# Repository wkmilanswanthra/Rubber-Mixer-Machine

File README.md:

# Rubber Mixer v1.0

## :eyes: Special considerations when uploading code
* Always create a **_new branch_** to upload new and edited code
* Fetch origin before making any changes to your code
* Add a well written description to each commit
* Mention every single change done
* Create a pull request and merge the branch in the main after resolving any conflicts
* If you face any problems when merging a branch watch [this video](https://youtu.be/9j0AOrO0dnw?t=1086) or contact me :full_moon_with_face: 
* Use the seperate folder named "Proteus files" to upload any proteus project files 
* Use the seperate folder named "test2" to upload new or changed header files 

## Components that need to be completed
* - [ ] Code for the Ultrasonic sensor (Detect the liquid levels once before the LCD Display starts)
* - [ ] Code for the calculation of pH values and required volumes

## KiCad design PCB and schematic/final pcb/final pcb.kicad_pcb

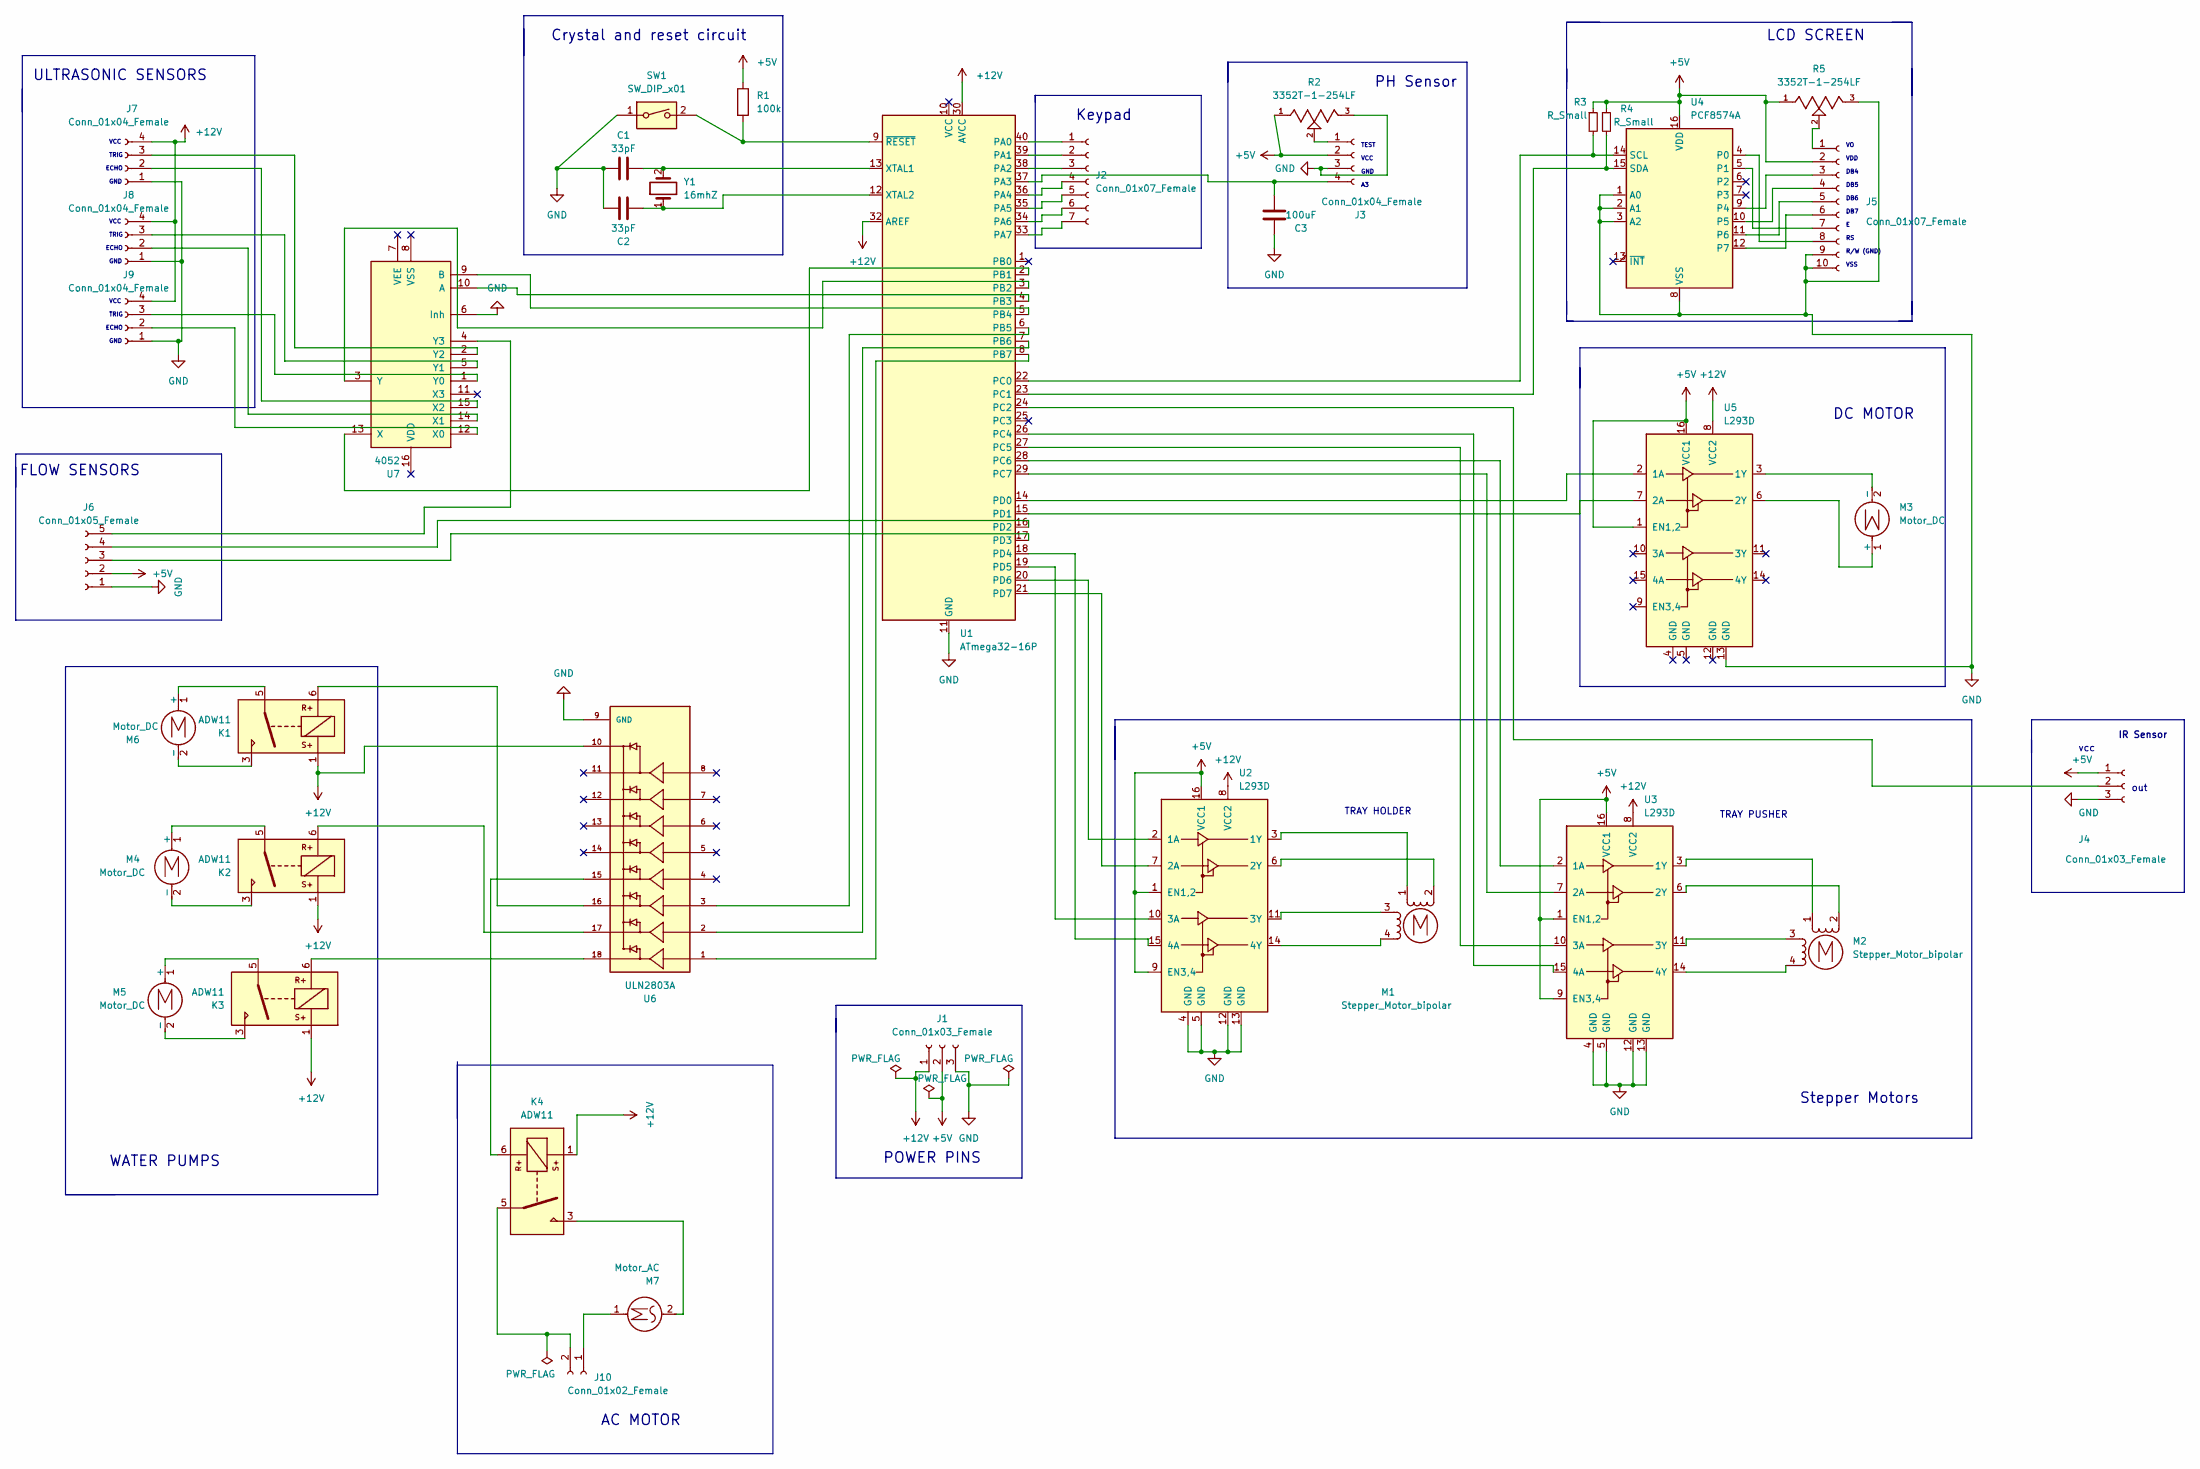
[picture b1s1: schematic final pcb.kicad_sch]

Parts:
C1: 33pF; C_Disc_D7.0mm_W2.5mm_P5.00mm
C2: 33pF; C_Disc_D7.5mm_W2.5mm_P5.00mm
C3: 100uF; C_Disc_D7.5mm_W2.5mm_P5.00mm
J1: Conn_01x03_Female; JST_EH_S3B-EH_1x03_P2.50mm_Horizontal
J2: Conn_01x07_Female; JST_EH_S7B-EH_1x07_P2.50mm_Horizontal
J3: Conn_01x04_Female; SolderWire-0.1sqmm_1x04_P3.6mm_D0.4mm_OD1mm
J4: Conn_01x03_Female; PinHeader_1x03_P2.54mm_Horizontal
J5: Conn_01x07_Female; JST_EH_S10B-EH_1x10_P2.50mm_Horizontal
J6: Conn_01x05_Female; JST_EH_S5B-EH_1x05_P2.50mm_Horizontal
J7, J8, J9: Conn_01x04_Female; JST_EH_S4B-EH_1x04_P2.50mm_Horizontal
J10: Conn_01x02_Female; JST_EH_B2B-EH-A_1x02_P2.50mm_Vertical
K1, K2, K3, K4: ADW11; Relay_1P1T_NO_10x24x18.8mm_Panasonic_ADW11xxxxW_THT
M1, M2: Stepper_Motor_bipolar; PinHeader_1x04_P2.54mm_Horizontal
M3, M4, M5, M6: Motor_DC; PinHeader_1x02_P2.54mm_Horizontal
M7: Motor_AC; PinHeader_1x02_P2.54mm_Horizontal
R1: 100k; R_Axial_DIN0204_L3.6mm_D1.6mm_P7.62mm_Horizontal
R2, R5: 3352T-1-254LF; TRIM_3352T-1-254LF; PARTREV 08/19
R3, R4: R_Small; R_0402_1005Metric
SW1: SW_DIP_x01; SW_DIP_SPSTx01_Slide_6.7x4.1mm_W7.62mm_P2.54mm_LowProfile
U1: ATmega32-16P; DIP-40_W15.24mm
U2, U3, U5: L293D; DIP-16_W7.62mm
U4: PCF8574A; SOIC127P1030X265-16N
U6: ULN2803A; DIP850W46P254L2324H393Q18; PARTREV 4
U7: 4052; DIP794W45P254L1969H508Q16
Y1: 16mhZ; Crystal_C38-LF_D3.0mm_L8.0mm_Vertical

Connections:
+5V: J1.2, J3.2, J4.1, J5.2, J6.2, R1.1, R2.1, R3.1, R4.1, R5.1, U2.1 (EN1,2), U2.9 (EN3,4), U2.16 (VCC1), U3.1 (EN1,2), U3.9 (EN3,4), U3.16 (VCC1), U4.16 (VDD), U5.1 (EN1,2), U5.16 (VCC1)
+12V: J1.1, J7.4, J8.4, J9.4, K1.1, K2.1, K3.1, K4.1, U1.30 (AVCC), U1.32 (AREF), U2.8 (VCC2), U3.8 (VCC2), U5.8 (VCC2), U6.10
GND: C1.2, C2.2, C3.2, J1.3, J3.3, J4.3, J5.9, J5.10, J6.1, J7.1, J8.1, J9.1, R2.3, R5.3, SW1.1, U1.11 (GND), U1.31 (GND), U2.4 (GND), U2.5 (GND), U2.12 (GND), U2.13 (GND), U3.4 (GND), U3.5 (GND), U3.12 (GND), U3.13 (GND), U4.1 (A0), U4.2 (A1), U4.3 (A2), U4.8 (VSS), U5.13 (GND), U6.9 (GND), U7.6 (Inh)
unnamed: C1.1, U1.13 (XTAL1), Y1.2
unnamed: C2.1, U1.12 (XTAL2), Y1.1
unnamed: C3.1, J3.4, U1.37 (PA3)
unnamed: J2.1, U1.40 (PA0)
unnamed: J2.2, U1.39 (PA1)
unnamed: J2.3, U1.38 (PA2)
unnamed: J2.4, U1.36 (PA4)
unnamed: J2.5, U1.35 (PA5)
unnamed: J2.6, U1.34 (PA6)
unnamed: J2.7, U1.33 (PA7)
unnamed: J3.1, R2.2
unnamed: J4.2, U1.24 (PC2)
unnamed: J5.1, R5.2
unnamed: J5.3, U4.9 (P4)
unnamed: J5.4, U4.10 (P5)
unnamed: J5.5, U4.11 (P6)
unnamed: J5.6, U4.12 (P7)
unnamed: J5.7, U4.5 (P1)
unnamed: J5.8, U4.4 (P0)
unnamed: J6.3, U1.17 (PD3)
unnamed: J6.4, U1.16 (PD2)
unnamed: J6.5, U7.4 (Y3)
unnamed: J7.2, U7.15 (X2)
unnamed: J7.3, U7.2 (Y2)
unnamed: J8.2, U7.14 (X1)
unnamed: J8.3, U7.5 (Y1)
unnamed: J9.2, U7.12 (X0)
unnamed: J9.3, U7.1 (Y0)
unnamed: J10.1, M7.1
unnamed: J10.2, K4.5
unnamed: K1.3, M6.2 (-)
unnamed: K1.5, M6.1 (+)
unnamed: K1.6, U6.16
unnamed: K2.3, M4.2 (-)
unnamed: K2.5, M4.1 (+)
unnamed: K2.6, U6.17
unnamed: K3.3, M5.2 (-)
unnamed: K3.5, M5.1 (+)
unnamed: K3.6, U6.18
unnamed: K4.3, M7.2
unnamed: K4.6, U6.15
unnamed: M1.1, U2.3 (1Y)
unnamed: M1.2 (-), U2.6 (2Y)
unnamed: M1.3, U2.11 (3Y)
unnamed: M1.4, U2.14 (4Y)
unnamed: M2.1, U3.3 (1Y)
unnamed: M2.2 (-), U3.6 (2Y)
unnamed: M2.3, U3.11 (3Y)
unnamed: M2.4, U3.14 (4Y)
unnamed: M3.1 (+), U5.6 (2Y)
unnamed: M3.2 (-), U5.3 (1Y)
unnamed: R1.2, SW1.2, U1.9 (~RESET)
unnamed: R3.2, U1.22 (PC0), U4.14 (SCL)
unnamed: R4.2, U1.23 (PC1), U4.15 (SDA)
unnamed: U1.2 (PB1), U7.13 (X)
unnamed: U1.3 (PB2), U7.3 (Y)
unnamed: U1.4 (PB3), U7.10 (A)
unnamed: U1.5 (PB4), U7.9 (B)
unnamed: U1.6 (PB5), U6.3
unnamed: U1.7 (PB6), U6.2
unnamed: U1.8 (PB7), U6.1
unnamed: U1.14 (PD0), U5.2 (1A)
unnamed: U1.15 (PD1), U5.7 (2A)
unnamed: U1.18 (PD4), U2.15 (4A)
unnamed: U1.19 (PD5), U2.10 (3A)
unnamed: U1.20 (PD6), U2.2 (1A)
unnamed: U1.21 (PD7), U2.7 (2A)
unnamed: U1.26 (PC4), U3.15 (4A)
unnamed: U1.27 (PC5), U3.10 (3A)
unnamed: U1.28 (PC6), U3.2 (1A)
unnamed: U1.29 (PC7), U3.7 (2A)

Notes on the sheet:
TRIG
GND
TRAY PUSHER
DC MOTOR
VCC
R/W (GND)
VSS
out
VDD
AC MOTOR
FLOW SENSORS
ECHO
DB5
DB7
PH Sensor
LCD SCREEN
DB4
Crystal and reset circuit
IR Sensor
vcc
ULTRASONIC SENSORS
TRAY HOLDER
WATER PUMPS
TEST
Keypad
POWER PINS
Stepper Motors
DB6

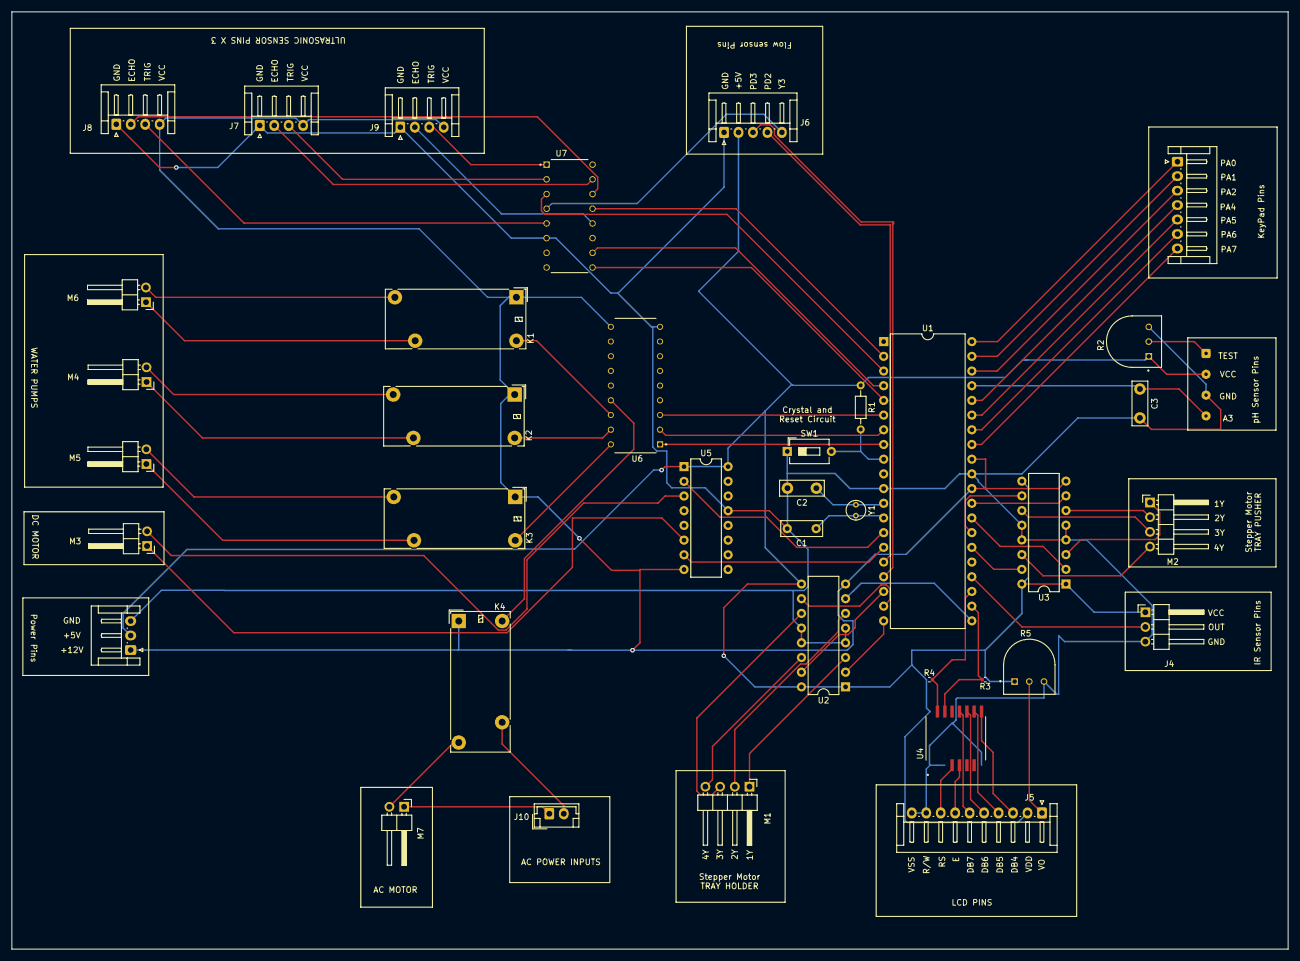
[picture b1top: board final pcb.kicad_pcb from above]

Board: 2 copper layers, 220.6 x 162.0 mm, 38 parts (0 on the bottom side), 74 nets.

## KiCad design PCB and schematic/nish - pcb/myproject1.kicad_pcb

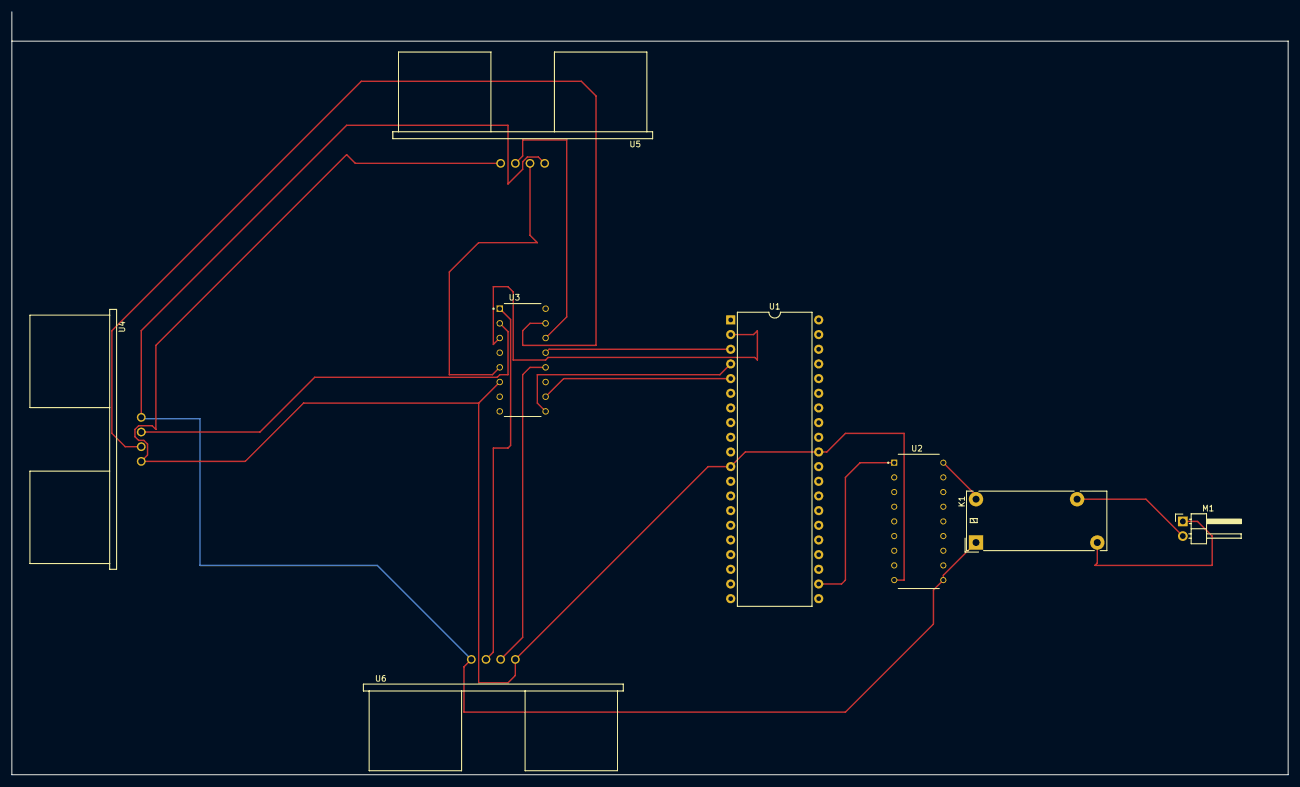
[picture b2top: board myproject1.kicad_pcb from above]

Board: 2 copper layers, 221.0 x 132.1 mm, 8 parts (0 on the bottom side), 16 nets.

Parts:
K1: ADW11; Relay_1P1T_NO_10x24x18.8mm_Panasonic_ADW11xxxxW_THT
M1: Motor_AC; PinHeader_1x02_P2.54mm_Horizontal
U1: ATmega32L-8P; DIP-40_W15.24mm
U2: ULN2803A; DIP850W46P254L2324H393Q18
U3: CD4052B; DIP794W45P254L1969H508Q16
U4, U5, U6: HC-SR04; XCVR_HC-SR04

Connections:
+12V: K1.1, U2.10 (COM), U4.1 (VCC), U5.1 (VCC), U6.1 (VCC)
AC: K1.5, M1.2
Earth: U1.11 (GND), U1.31 (GND), U2.9 (GND), U3.6 (INH), U4.4 (GND), U5.4 (GND), U6.4 (GND)
unnamed: K1.3, M1.1
unnamed: K1.6, U2.18 (O1)
unnamed: U1.2 (PB1), U3.3 (Y)
unnamed: U1.3 (PB2), U3.13 (X)
unnamed: U1.4 (PB3), U3.9 (B)
unnamed: U1.5 (PB4), U3.10 (A)
unnamed: U1.22 (PC0), U2.1 (I1)
unnamed: U3.1 (Y0), U6.2 (TRIG)
unnamed: U3.2 (Y2), U4.2 (TRIG)
unnamed: U3.5 (Y1), U5.2 (TRIG)
unnamed: U3.12 (X0), U6.3 (ECHO)
unnamed: U3.14 (X1), U5.3 (ECHO)
unnamed: U3.15 (X2), U4.3 (ECHO)

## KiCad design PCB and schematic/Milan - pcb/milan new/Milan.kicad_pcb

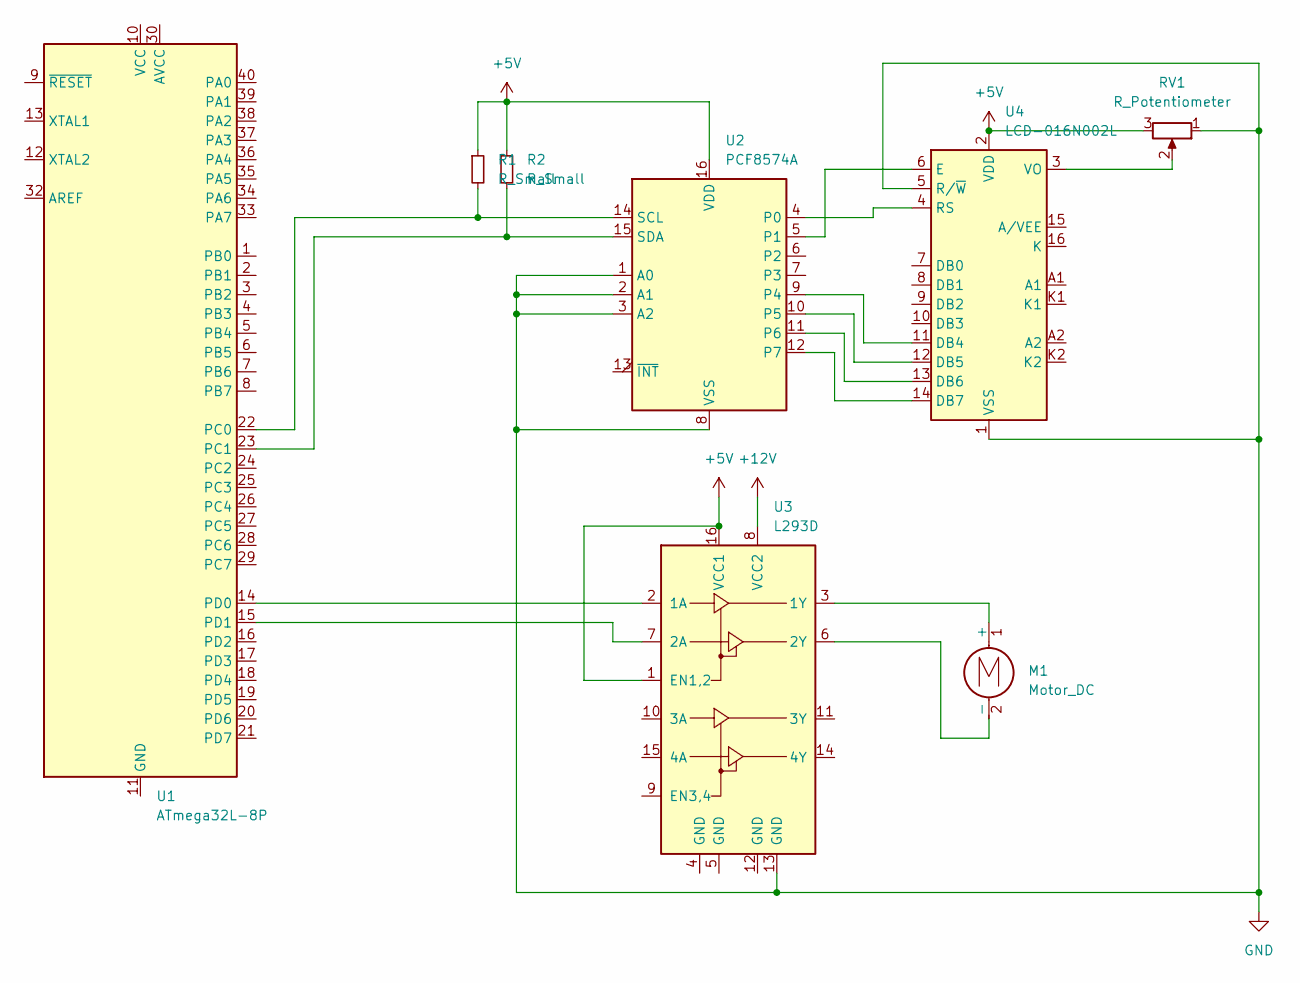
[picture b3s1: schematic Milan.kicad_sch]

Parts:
M1: Motor_DC; PinHeader_1x02_P2.54mm_Horizontal
R1, R2: R_Small; R_0402_1005Metric
RV1: R_Potentiometer; Potentiometer_ACP_CA6-VSMD_Vertical
U1: ATmega32L-8P; DIP-40_W15.24mm
U2: PCF8574A; DIL16
U3: L293D; DIP-16_W7.62mm
U4: LCD-016N002L

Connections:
+5V: R1.1, R2.1, RV1.3, U2.16 (VDD), U3.1 (EN1,2), U3.16 (VCC1), U4.2 (VDD)
+12V: U3.8 (VCC2)
GND: RV1.1, U2.1 (A0), U2.2 (A1), U2.3 (A2), U2.8 (VSS), U3.13 (GND), U4.1 (VSS), U4.5 (R/~W)
unnamed: M1.1 (+), U3.3 (1Y)
unnamed: M1.2 (-), U3.6 (2Y)
unnamed: U1.11 (GND), U1.31 (GND)
unnamed: U1.14 (PD0), U3.2 (1A)
unnamed: U1.15 (PD1), U3.7 (2A)
unnamed: R1.2, U1.22 (PC0), U2.14 (SCL)
unnamed: R2.2, U1.23 (PC1), U2.15 (SDA)
unnamed: U2.4 (P0), U4.4 (RS)
unnamed: U2.5 (P1), U4.6 (E)
unnamed: U2.9 (P4), U4.11 (DB4)
unnamed: U2.10 (P5), U4.12 (DB5)
unnamed: U2.11 (P6), U4.13 (DB6)
unnamed: U2.12 (P7), U4.14 (DB7)
unnamed: RV1.2, U4.3 (VO)

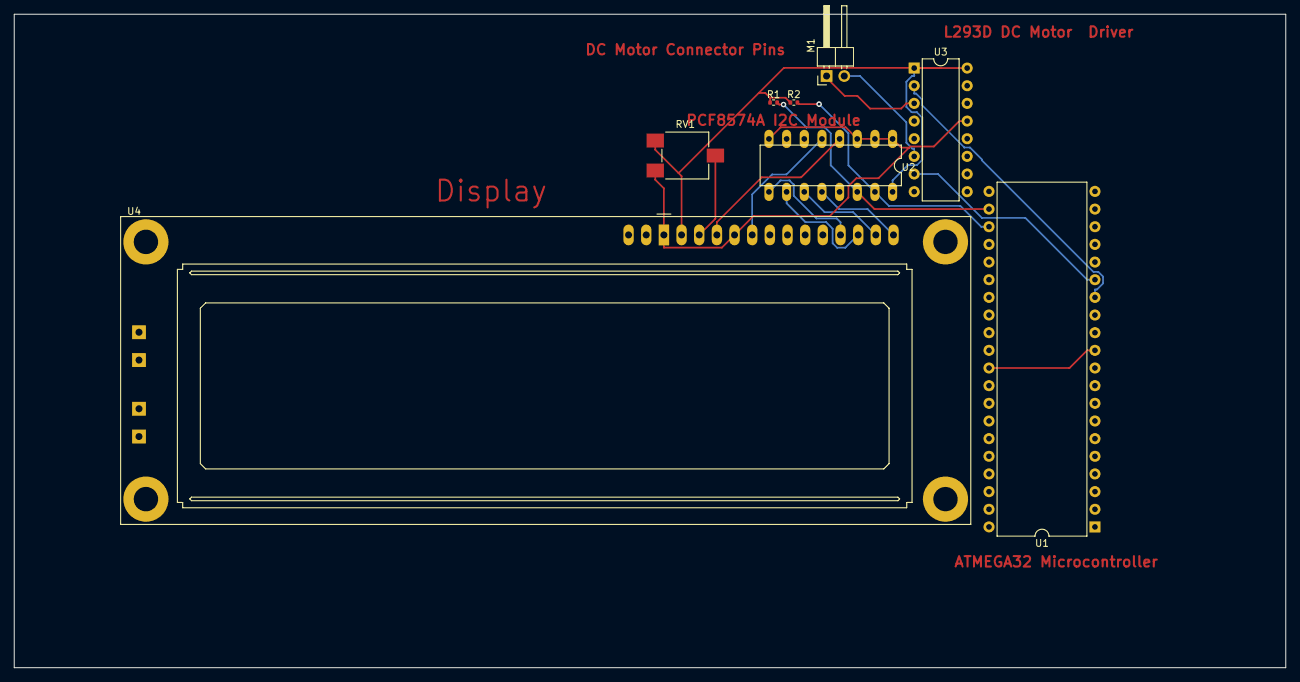
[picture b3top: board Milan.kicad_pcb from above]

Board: 2 copper layers, 182.9 x 94.0 mm, 8 parts (0 on the bottom side), 16 nets.

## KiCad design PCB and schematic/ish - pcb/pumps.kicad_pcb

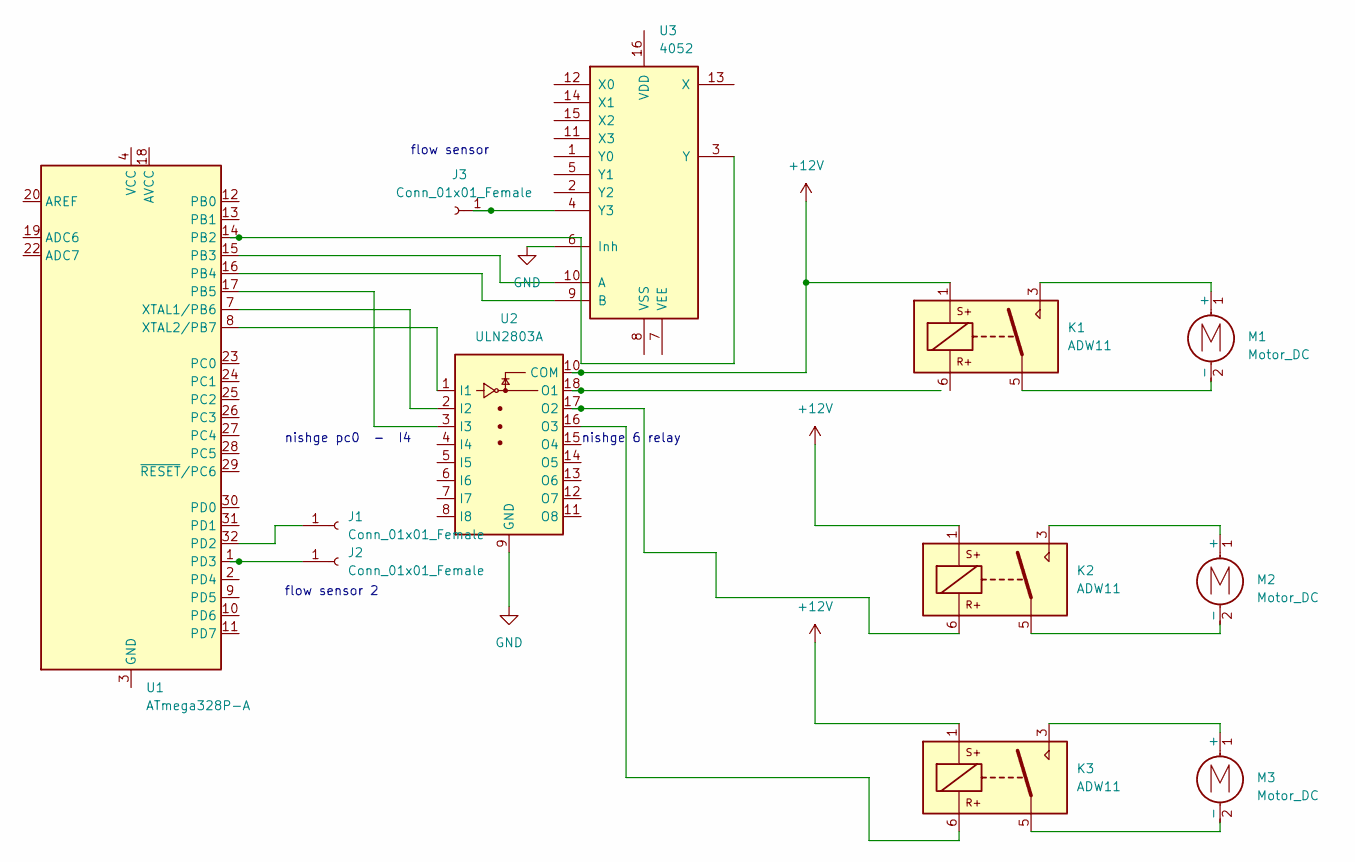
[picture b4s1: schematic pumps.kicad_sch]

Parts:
J1, J2, J3: Conn_01x01_Female; PinHeader_1x02_P1.00mm_Horizontal
K1, K2, K3: ADW11; Relay_1P1T_NO_10x24x18.8mm_Panasonic_ADW11xxxxW_THT
M1, M2, M3: Motor_DC; PinHeader_1x02_P2.54mm_Horizontal
U1: ATmega328P-A; TQFP-32_7x7mm_P0.8mm
U2: ULN2803A; DIP850W46P254L2324H393Q18
U3: 4052; DIP794W45P254L1969H508Q16

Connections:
+12V: K1.1, K2.1, K3.1, U2.10 (COM)
GND: U2.9 (GND), U3.6 (Inh)
unnamed: K1.3, M1.1 (+)
unnamed: K1.5, M1.2 (-)
unnamed: K2.3, M2.1 (+)
unnamed: K2.5, M2.2 (-)
unnamed: K2.6, U2.17 (O2)
unnamed: K3.3, M3.1 (+)
unnamed: K3.5, M3.2 (-)
unnamed: K3.6, U2.16 (O3)
unnamed: J2.1, U1.1 (PD3)
unnamed: U1.4 (VCC), U1.6 (VCC)
unnamed: U1.7 (XTAL1/PB6), U2.2 (I2)
unnamed: U1.8 (XTAL2/PB7), U2.1 (I1)
unnamed: U1.14 (PB2), U3.3 (Y)
unnamed: U1.15 (PB3), U3.10 (A)
unnamed: U1.16 (PB4), U3.9 (B)
unnamed: U1.17 (PB5), U2.3 (I3)
unnamed: U1.3 (GND), U1.5 (GND), U1.21 (GND)
unnamed: J1.1, U1.32 (PD2)
unnamed: J3.1, U3.4 (Y3)

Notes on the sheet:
nishge pc0 - I4
nishge 6 relay
flow sensor
flow sensor 2

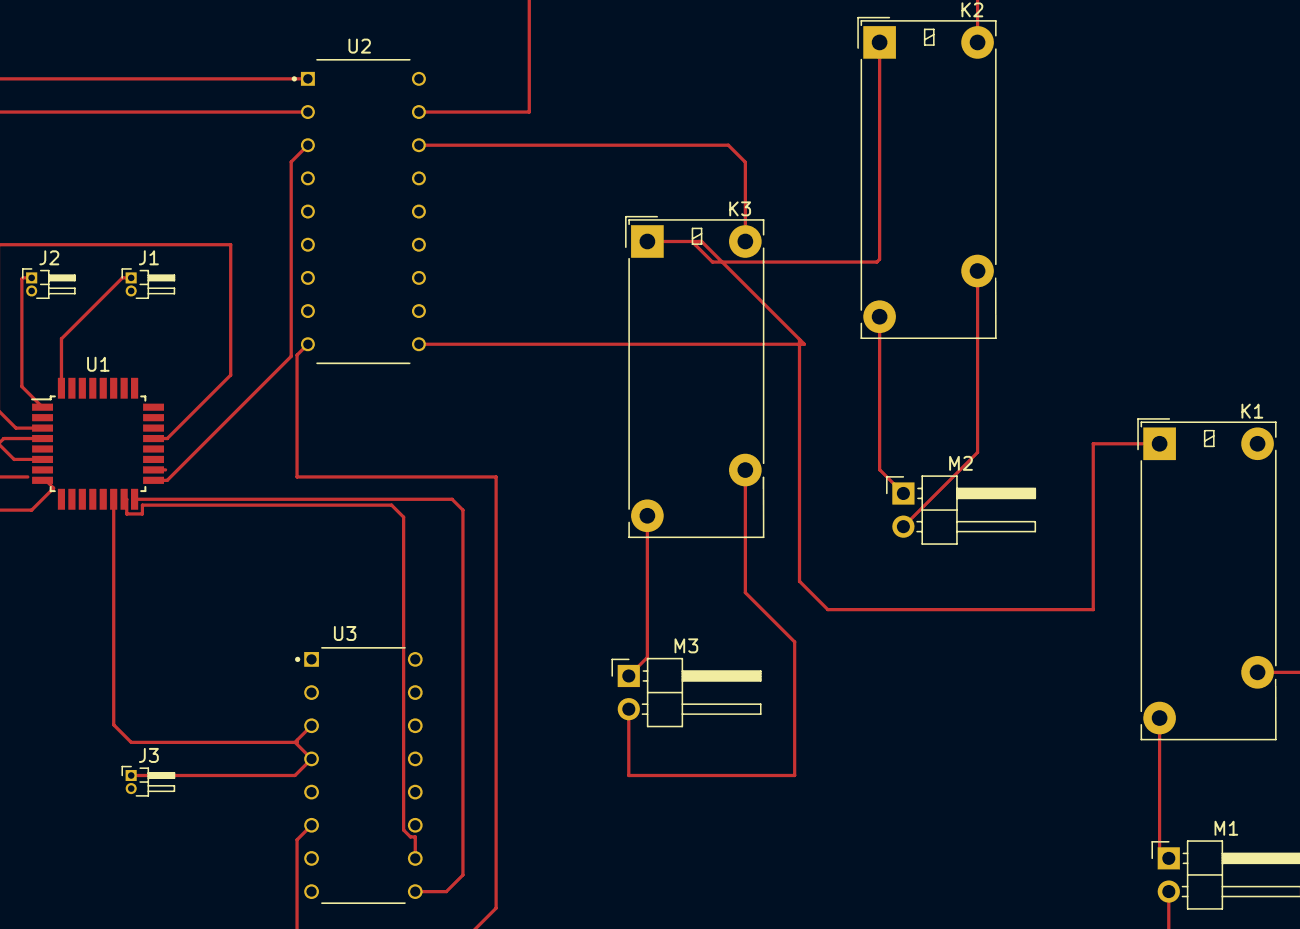
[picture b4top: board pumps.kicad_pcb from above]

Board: 2 copper layers, 12 parts (0 on the bottom side), 21 nets.

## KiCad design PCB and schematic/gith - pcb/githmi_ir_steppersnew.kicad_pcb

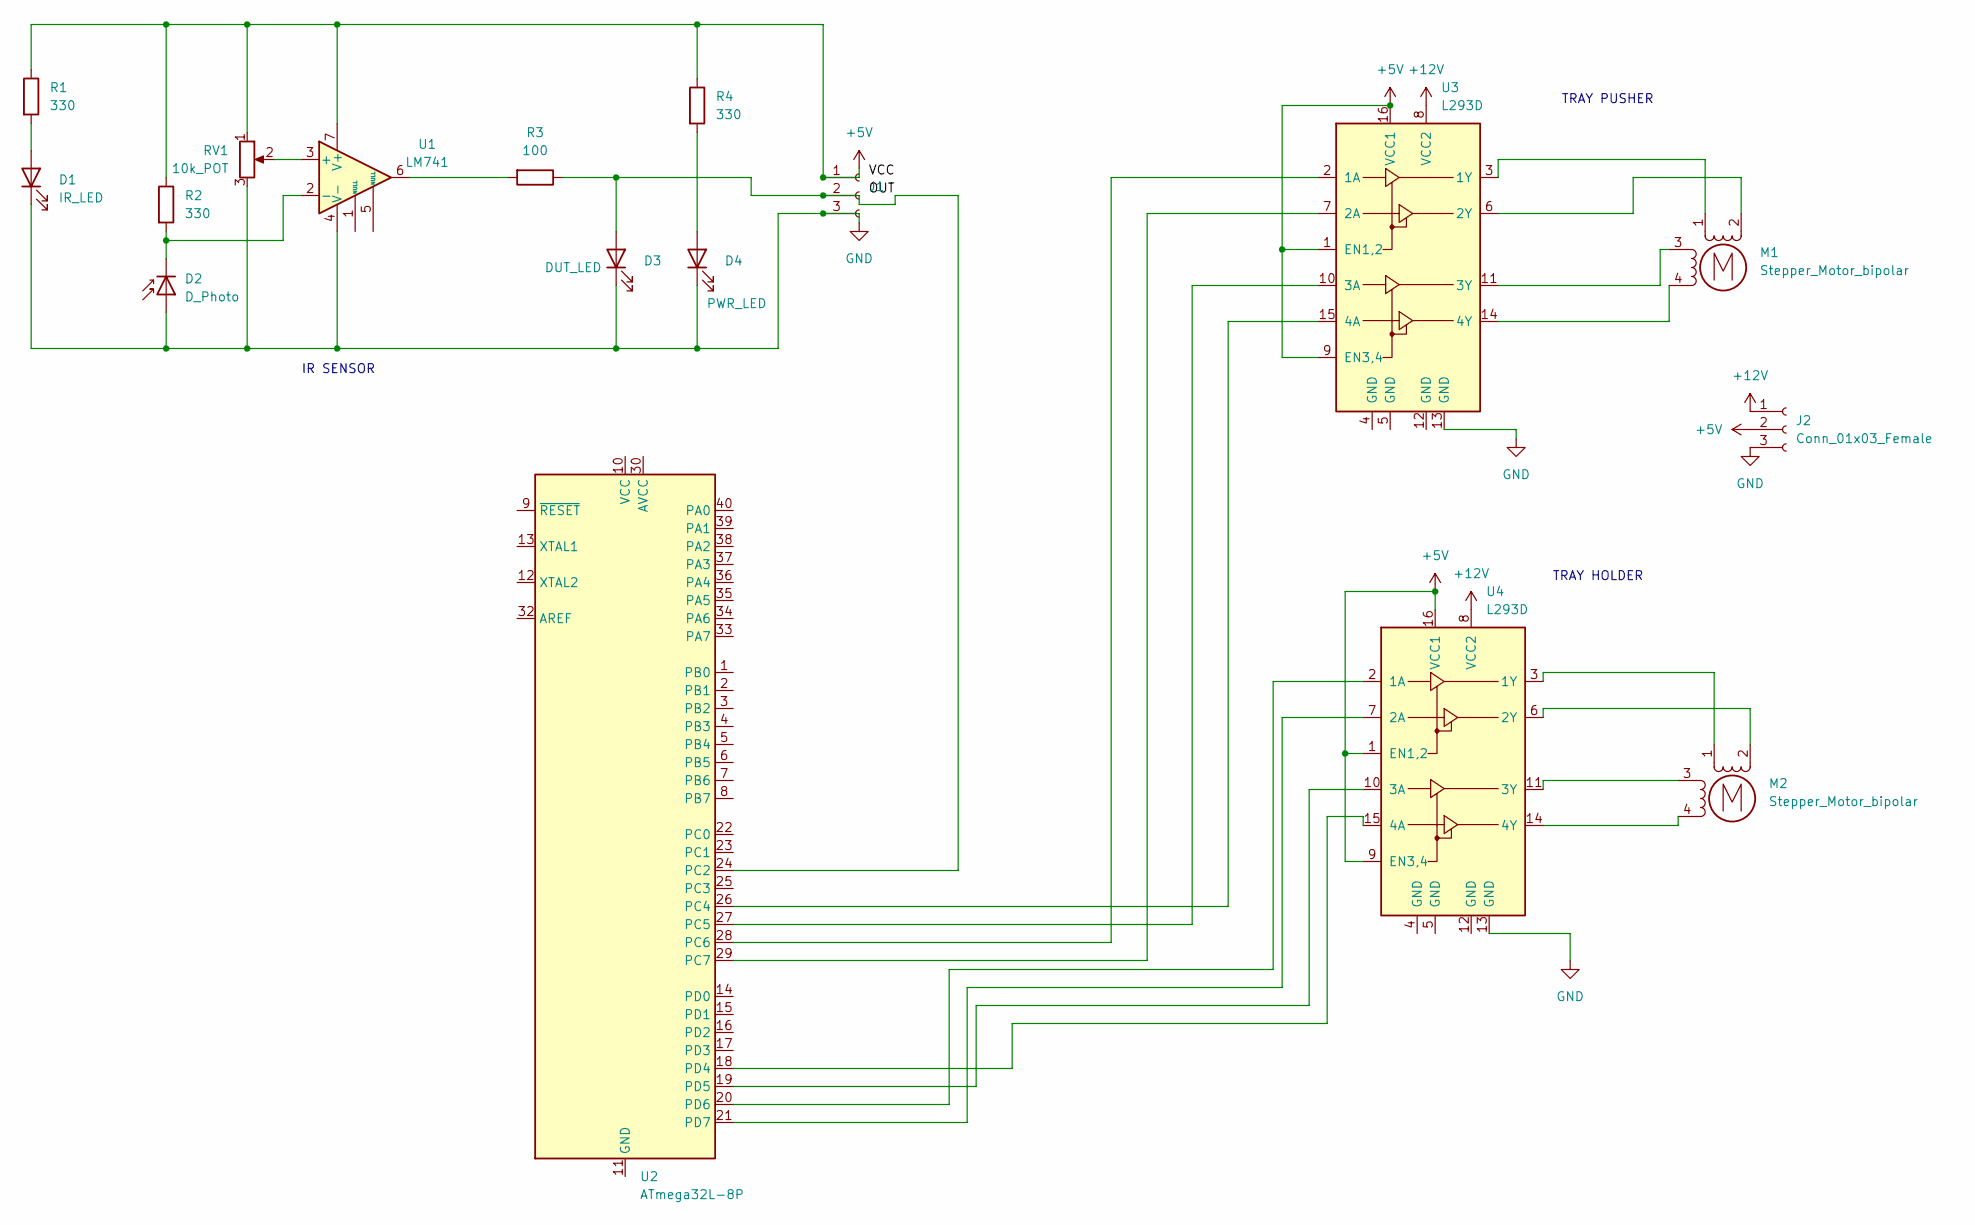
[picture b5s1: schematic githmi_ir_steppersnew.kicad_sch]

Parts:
D1: IR_LED; LED_D3.0mm_Horizontal_O1.27mm_Z2.0mm
D2: D_Photo; LED_D3.0mm_Horizontal_O1.27mm_Z2.0mm_IRBlack
D3: DUT_LED; LED_0805_2012Metric_Pad1.15x1.40mm_HandSolder
D4: PWR_LED; LED_0805_2012Metric_Pad1.15x1.40mm_HandSolder
J1: (no value)
J2: Conn_01x03_Female; SolderWire-0.1sqmm_1x03_P3.6mm_D0.4mm_OD1mm
M1, M2: Stepper_Motor_bipolar
R1, R2, R4: 330; R_0805_2012Metric
R3: 100; R_0805_2012Metric
RV1: 10k_POT; Potentiometer_ACP_CA9-V10_Vertical_Hole
U1: LM741; SOIC-8_3.9x4.9mm_P1.27mm
U2: ATmega32L-8P; DIP-40_W15.24mm
U3, U4: L293D; DIP-16_W7.62mm

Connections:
+5V: J1.1, J2.2, R1.1, R2.1, R4.1, RV1.1, U1.7 (V+), U3.1 (EN1,2), U3.9 (EN3,4), U3.16 (VCC1), U4.1 (EN1,2), U4.9 (EN3,4), U4.16 (VCC1)
+12V: J2.1, U3.8 (VCC2), U4.8 (VCC2)
GND: D1.1 (K), D2.2 (A), D3.1 (K), D4.1 (K), J1.3, J2.3, RV1.3, U1.4 (V-), U3.13 (GND), U4.13 (GND)
unnamed: D1.2 (A), R1.2
unnamed: D2.1 (K), R2.2, U1.2 (-)
unnamed: D3.2 (A), J1.2, R3.1, U2.24 (PC2)
unnamed: D4.2 (A), R4.2
unnamed: M1.1, U3.3 (1Y)
unnamed: M1.2 (-), U3.6 (2Y)
unnamed: M1.3, U3.11 (3Y)
unnamed: M1.4, U3.14 (4Y)
unnamed: M2.1, U4.3 (1Y)
unnamed: M2.2 (-), U4.6 (2Y)
unnamed: M2.3, U4.11 (3Y)
unnamed: M2.4, U4.14 (4Y)
unnamed: R3.2, U1.6
unnamed: RV1.2, U1.3 (+)
unnamed: U2.11 (GND), U2.31 (GND)
unnamed: U2.18 (PD4), U4.15 (4A)
unnamed: U2.19 (PD5), U4.10 (3A)
unnamed: U2.20 (PD6), U4.2 (1A)
unnamed: U2.21 (PD7), U4.7 (2A)
unnamed: U2.26 (PC4), U3.15 (4A)
unnamed: U2.27 (PC5), U3.10 (3A)
unnamed: U2.28 (PC6), U3.2 (1A)
unnamed: U2.29 (PC7), U3.7 (2A)

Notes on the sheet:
TRAY HOLDER
TRAY PUSHER
IR SENSOR

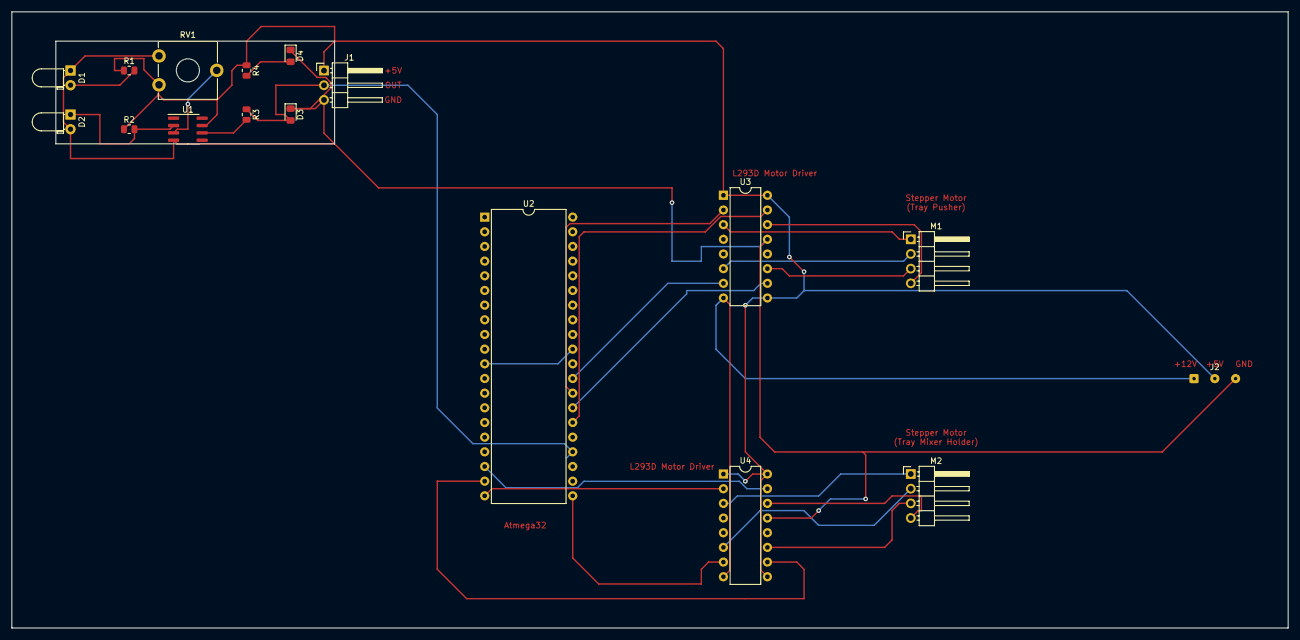
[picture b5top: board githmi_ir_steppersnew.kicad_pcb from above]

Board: 2 copper layers, 221.0 x 106.7 mm, 17 parts (0 on the bottom side), 26 nets.

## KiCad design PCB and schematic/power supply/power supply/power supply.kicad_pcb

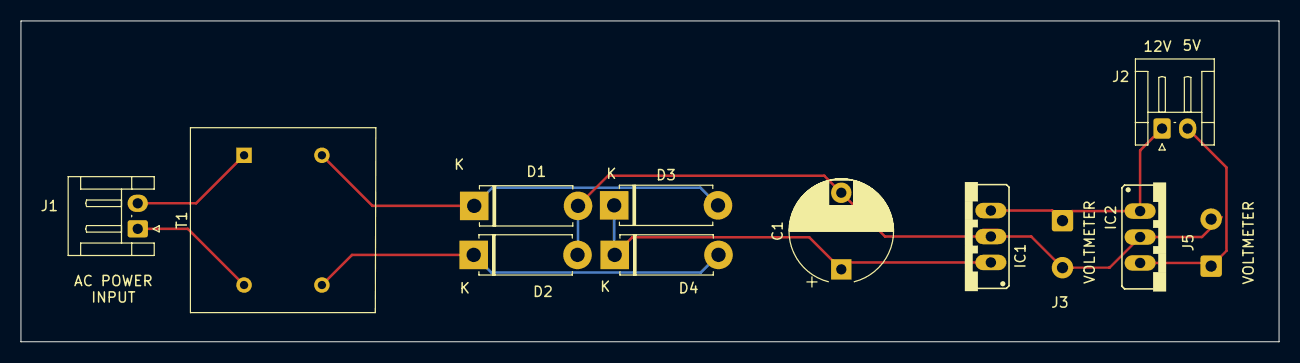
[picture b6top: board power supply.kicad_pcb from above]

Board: 2 copper layers, 123.1 x 31.4 mm, 12 parts (0 on the bottom side), 7 nets.

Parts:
C1: C_Polarized; CP_Radial_D10.0mm_P7.50mm
D1, D2, D3, D4: D; D_5W_P10.16mm_Horizontal
IC1, IC2: L7812; 78XXS
J1, J2: Conn_01x02_Female; JST_EH_S2B-EH_1x02_P2.50mm_Horizontal
J3, J5: Conn_01x02_Female; SolderWire-0.5sqmm_1x02_P4.6mm_D0.9mm_OD2.1mm
T1: Transformer_1P_1S; Transformer_NF_ETAL_P3324

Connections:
-VDC: C1.2, D1.2 (A), D2.2 (A), IC1.GND, IC2.GND, J3.2, J5.2
unnamed: D1.1 (K), D3.2 (A), T1.3 (SB)
unnamed: D2.1 (K), D4.2 (A), T1.4 (SA)
unnamed: IC1.OUT, IC2.IN, J2.1, J3.1
unnamed: IC2.OUT, J2.2, J5.1
VAC: J1.1, J1.2, T1.1 (AA), T1.6 (AB)
VS: C1.1, D3.1 (K), D4.1 (K), IC1.IN

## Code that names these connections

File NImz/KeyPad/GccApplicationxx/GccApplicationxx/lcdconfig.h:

#ifndef	LCDCONFIG_H_
#define LCDCONFIG_H_

/***************************************************************************

The four data lines as well as the two control lines may be
implemented on any available I/O pin of any port.  These are
the connections used for this program:

-----------                   ----------
| ATmega32  |                 |   LCD    |
|           |                 |          |
|        PA7|---------------->|D7        |
|        PA6|---------------->|D6        |
|        PA5|---------------->|D5        |
|        PA4|---------------->|D4        |
|           |                 |D3        |
|           |                 |D2        |
|           |                 |D1        |
|           |                 |D0        |
|           |                 |          |
|        PB3|---------------->|E         |
|        PB2|---------------->|RW        |
|        PB1|---------------->|RS        |
-----------                   ----------

**************************************************************************/

#define LCD_PORT_D7     	PORTB
#define LCD_DDR_D7      	DDRB
#define D7_BIT				7

#define LCD_PORT_D6     	PORTB
#define LCD_DDR_D6      	DDRB
#define D6_BIT				6

#define LCD_PORT_D5     	PORTB
#define LCD_DDR_D5      	DDRB
#define D5_BIT				5

#define LCD_PORT_D4     	PORTB
#define LCD_DDR_D4      	DDRB
#define D4_BIT				4

//lcd Enable pin
#define E_PORT				PORTB
#define E_BIT				1
#define E_DDR				DDRB
//lcd Register Select pin
#define RS_PORT				PORTB
#define RS_BIT				0
#define RS_DDR				DDRB
//lcd Register Select pin
#define RW_PORT				PORTB
#define RW_BIT				2
#define RW_DDR				DDRB
 
#endif // LCDCONFIG_H_

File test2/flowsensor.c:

#include "flowsensor.h"

float calibrationFactor = 4.5;
float flowRate=0;
volatile unsigned int pulseCount1=0;
volatile unsigned int pulseCount2=0;
volatile unsigned int pulseCount3=0;
unsigned long oldTime=0;
unsigned int flowMilliLitres=0;
unsigned long totalMilliLitres=0;
volatile unsigned long int millisec=0;
volatile unsigned long int sec=0;
int v_water =1000 ;
int v_latex = 1000;
int v_acid ;


void timer_1(){

	TCCR1A =(0 << WGM11)| (0 << WGM10 );// CTC
	TIMSK |= (1 << OCIE1A);//Set interrupt on compare match
	TCCR1B |= (1 << CS12) | (1 << CS10);// set pre scaler to 1024 and start the timer
	OCR1A = 0x07;
}

void pump_w(){
	
	PORTB = PORTB | (1<<5);    /* Turn on the Relay and motor ON*/
	timer_1();
	DDRD &= ~(1 << DDD2);     /*Clear the PD2 pin*/
	PORTD =	 0xFF;             /* turn On the Pull-up */
	DDRD &= ~(1<<PD2);        /* Make INT0 pin as Input */
	GICR = (1<<INT0);         /* Enable INT0*/
	MCUCR = ((1<<ISC00)|(1<<ISC01));/* Trigger INT0 on Rising Edge triggered */
	
	sei();                   /*enable interrupts*/
	while (totalMilliLitres!=v_water)   {
		if((millisec-oldTime)>=1000)
		{
			sec++;
			if(sec==1)
			{
				cli();
				
				flowRate = ((1000.0 / (millisec - oldTime)) * pulseCount1) / calibrationFactor;
				oldTime = millisec;
				flowMilliLitres = (flowRate / 60) * 1000;
				totalMilliLitres += flowMilliLitres;
				
				millisec=0;
				sec=0;
				pulseCount1 = 0;

				sei();
			}
		}
	}
	PORTB = PORTB & (~(1<<5)); /*Turn off the relay*/
	
}
ISR (TIMER1_COMPA_vect){
	millisec++;
}
ISR (INT0_vect){
	pulseCount1++;
}

void pump_l(){
	PORTB = PORTB | (1<<6); /* Turn on the Relay and motor ON*/
	timer_1();
	DDRD &= ~(1 << DDD2);     // Clear the PD2 pin
	PORTD = 0xFF;   // turn On the Pull-up
	DDRD &= ~(1<<PD3);		/* Make INT1 pin as Input */
	GICR = (1<<INT1);		/* Enable INT1*/
	MCUCR = ((1<<ISC10)|(1<<ISC11));/* Trigger INT1 on Rising Edge triggered */

	sei();// enable interrupts
	
	while (totalMilliLitres!=v_latex)   {
		if((millisec-oldTime)>=1000)
		{
			sec++;
			if(sec==1)
			{
				cli();
				
				flowRate = ((1000.0 / (millisec - oldTime)) * pulseCount2) / calibrationFactor;
				oldTime = millisec;
				flowMilliLitres = (flowRate / 60) * 1000;
				totalMilliLitres += flowMilliLitres;

				millisec=0;
				sec=0;
				pulseCount2 = 0;

				sei();
			}
		}
	}
	PORTB = PORTB & (~(1<<6)); /*Turn off the relay*/
	
}


ISR (INT1_vect){
	pulseCount2++;
}

void pump_a( int vol){
	v_acid = vol;
	PORTB = PORTB | (0<<4);
	PORTB = PORTB | (0<<3);    /*multiplexer input*/
	PORTB = PORTB | (1<<7); /* Turn OFF the Relay and motor ON*/
	timer_1();
	DDRB &= ~(1 << DDB2);     // Clear the PD2 pin
	PORTB = 0xFF;   // turn On the Pull-up
	DDRB &= ~(1<<PB2);		/* Make INT2 pin as Input */
	GICR = (1<<INT2);		/* Enable INT2*/
	MCUCR = (1<<ISC2);/* Trigger INT2 on Rising Edge triggered */


	sei();// enable interrupts
	
	while (totalMilliLitres!=v_acid)   {
		if((millisec-oldTime)>=1000)
		{
			sec++;
			if(sec==1)
			{
				cli();
				
				flowRate = ((1000.0 / (millisec - oldTime)) * pulseCount3) / calibrationFactor;
				oldTime = millisec;
				flowMilliLitres = (flowRate / 60) * 1000;
				totalMilliLitres += flowMilliLitres;
				
				millisec=0;
				sec=0;
				pulseCount3 = 0;

				sei();
				
			}
		}
	}
	PORTB = PORTB & (~(1<<7)); /*Turn off the relay*/
	
}


/*ISR (INT2_vect){
	pulseCount3++;
}*/


//--------------------------------------------------Nishshanka's Code--------------------------------------
static volatile unsigned int tCount = 0;
static volatile int i = 0;
double distance = 0;


void initUS(){
	
	DDRB = DDRB | 1 << DDB1;
	//DDRD = DDRD & ~(1 << DDD2) ;
	//PORTD = PORTD & ~(1 << PD2);
	DDRB = DDRB & ~(1 << DDB2) ;
	PORTB = PORTB & ~(1 << PB2);
	DDRB= DDRB | 1 << DDB3;
	DDRB= DDRB | 1 << DDB4;
	_delay_ms(50);
	MCUCSR |= 1 << ISC2;
	GIFR &= ~(1<< INTF2);
	GICR |= 1<<INT2;
	//MCUCR |= 1<<ISC00;
	TIMSK |= 1 << TOIE1;
	sei();
}

uint8_t ultrasonic1()
{
	v_water=12;
	PORTB=PORTB & ~(1 << PB3);
	PORTB=PORTB & ~(1 << PB4);
	trigPulse();
	distance = tCount*1000000.0/F_CPU/58;
	v_water=13;
	return retDistance(distance);

}


uint8_t ultrasonic2()
{
	PORTB=PORTB | 1 << PB3;
	PORTB=PORTB & ~(1 << PB4);
	trigPulse();
	distance = tCount*1000000.0/F_CPU/58;
	return retDistance(distance);

}

uint8_t ultrasonic3()
{
	PORTB=PORTB & ~(1 << PB3);
	PORTB=PORTB | 1 << PB4;
	trigPulse();
	distance = tCount*1000000.0/F_CPU/58;
	return retDistance(distance);

}


void trigPulse()
{
	PORTB = PORTB | 1<<PB1;
	_delay_us(15);
	PORTB = PORTB & ~(1<<PB1);
	_delay_us(15);
	
}

uint8_t retDistance(double distance)
{
	v_acid =15;
	if (distance >50)
	{
		return 1;
	}
	else
	{
		return 0;
	}
	_delay_ms(200);
	
}

ISR(TIMER1_OVF_vect){
	TCCR1B = 0;
	tCount = 200;
	TCNT1 = 0;
	i = 0;
}

ISR(INT2_vect)
{
	GICR &= ~(1<<INT2);
	MCUCSR ^= 1 << ISC2;
	GIFR &= ~(1<< INTF2);
	GICR |= 1<<INT2;
	pulseCount3++;

	if(i == 0)
	{
		TCCR1B |= 1<<CS10;
		i = 1;
	}
	else
	{
		TCCR1B = 0;
		tCount = TCNT1;
		TCNT1 = 0;
		i = 0;
	}
}

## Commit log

2022-05-08 added ph 1 pin
2022-05-15 Updated main.c edited code in stpr motor fixed lcd
2022-05-20 4*3 Keypad
2022-05-22 Completed components as of 2022/05/22
2022-05-22 conflict
2022-05-22 Code compilation as of 2022-05-23
2022-05-23 Final Changes
2022-06-06 last proteus
2022-06-06 changes 2022.06.06
2022-06-06 final pcb
2022-06-06 githmi pcb
2022-06-06 ish pcb
2022-06-06 milan pcb
2022-06-06 nish pcb
2022-06-06 final pcb last
2022-06-06 power supply
2022-06-06 footprints
2022-06-10 individual pcb
